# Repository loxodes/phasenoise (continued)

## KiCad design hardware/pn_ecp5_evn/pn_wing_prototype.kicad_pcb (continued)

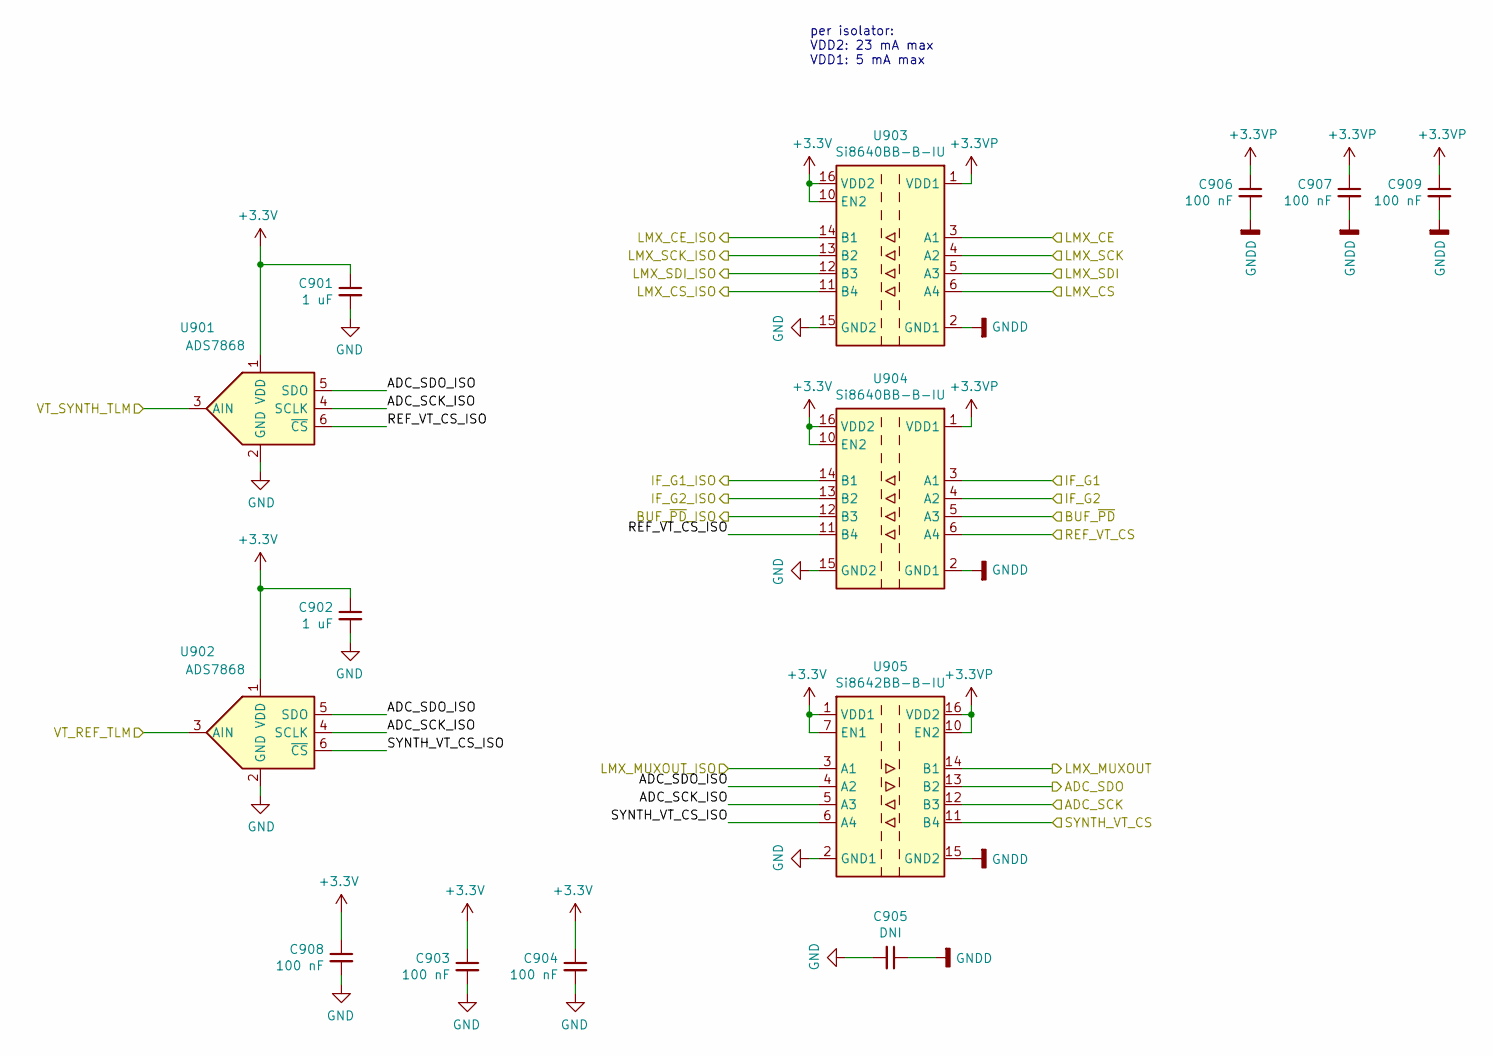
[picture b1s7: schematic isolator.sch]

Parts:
C901, C902: 1 uF; C_0402_1005Metric
C903, C904, C906, C907, C908, C909: 100 nF; C_0402_1005Metric
C905: DNI; C_0402_1005Metric
U901, U902: ADS7868; TSOT-23-6
U903, U904: Si8640BB-B-IU; QSOP-16_3.9x4.9mm_P0.635mm
U905: Si8642BB-B-IU; QSOP-16_3.9x4.9mm_P0.635mm

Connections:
+3.3VP: C906.1, C907.1, C909.1, U903.1 (VDD1), U904.1 (VDD1), U905.10 (EN2), U905.16 (VDD2); also elsewhere on the board
/BUF_~PD: U904.12 (B3); also elsewhere on the board
/IF_G1: U904.14 (B1); also elsewhere on the board
/IF_G2: U904.13 (B2); also elsewhere on the board
/LMX_CE: U903.14 (B1); also elsewhere on the board
/LMX_CSB: U903.11 (B4); also elsewhere on the board
/LMX_MUXout: U905.3 (A1); also elsewhere on the board
/LMX_SCK: U903.13 (B2); also elsewhere on the board
/LMX_SDI: U903.12 (B3); also elsewhere on the board
/VT_REF_TLM: U902.3 (AIN); also elsewhere on the board
/VT_SYNTH_TLM: U901.3 (AIN); also elsewhere on the board
/isolator/ADC_SCK: U905.12 (B3); also elsewhere on the board
/isolator/ADC_SCK_ISO: U901.4 (SCLK), U902.4 (SCLK), U905.5 (A3)
/isolator/ADC_SDO: U905.13 (B2); also elsewhere on the board
/isolator/ADC_SDO_ISO: U901.5 (SDO), U902.5 (SDO), U905.4 (A2)
/isolator/BUF_~PD: U904.5 (A3); also elsewhere on the board
/isolator/IF_G1: U904.3 (A1); also elsewhere on the board
/isolator/IF_G2: U904.4 (A2); also elsewhere on the board
/isolator/LMX_CE: U903.3 (A1); also elsewhere on the board
/isolator/LMX_CS: U903.6 (A4); also elsewhere on the board
/isolator/LMX_MUXOUT: U905.14 (B1); also elsewhere on the board
/isolator/LMX_SCK: U903.4 (A2); also elsewhere on the board
/isolator/LMX_SDI: U903.5 (A3); also elsewhere on the board
/isolator/REF_VT_CS: U904.6 (A4); also elsewhere on the board
/isolator/REF_VT_CS_ISO: U901.6 (~CS), U904.11 (B4)
/isolator/SYNTH_VT_CS: U905.11 (B4); also elsewhere on the board
/isolator/SYNTH_VT_CS_ISO: U902.6 (~CS), U905.6 (A4)
GND: C901.2, C902.2, C903.2, C904.2, C905.2, C908.2, U901.2 (GND), U902.2 (GND), U903.9 (GND2), U903.15 (GND2), U904.9 (GND2), U904.15 (GND2), U905.2 (GND1), U905.8 (GND1); also elsewhere on the board
GNDD: C905.1, C906.2, C907.2, C909.2, U903.2 (GND1), U903.8 (GND1), U904.2 (GND1), U904.8 (GND1), U905.9 (GND2), U905.15 (GND2); also elsewhere on the board

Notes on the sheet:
per isolator: VDD2: 23 mA max VDD1: 5 mA max

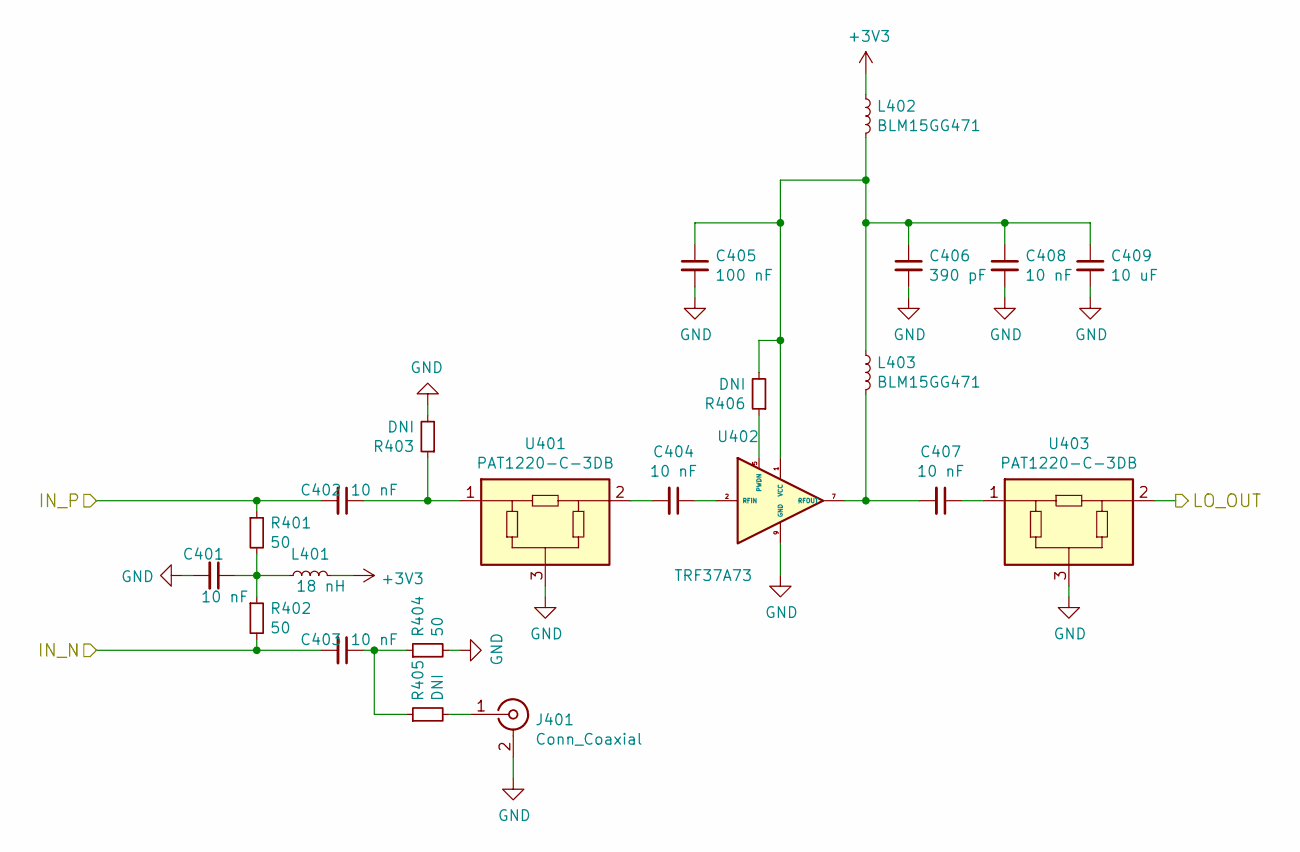
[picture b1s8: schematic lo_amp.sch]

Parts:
C301, C302, C303, C304, C307, C308: 10 nF; C_0402_1005Metric
C305: 100 nF; C_0402_1005Metric
C306: 390 pF; C_0603_1608Metric
C309: 10 uF; C_0603_1608Metric
J401: Conn_Coaxial; U.FL_Hirose_U.FL-R-SMT-1_Vertical
L301: 18 nH; L_0402_1005Metric
L302, L303: BLM15GG471; L_0402_1005Metric
R301, R302, R304: 50; R_0402_1005Metric
R303, R305, R306: DNI; R_0402_1005Metric
U301, U303: PAT1220-C-3DB; RF_Attenuator_Susumu_PAT1220
U302: TRF37A73; WSON-8-1EP_2x2mm_P0.5mm_EP0.9x1.6mm

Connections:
/rf_path/LO_IN: U303.2; also elsewhere on the board
/synth/lo_amp/IN_N: C303.2, R302.2; also elsewhere on the board
/synth/lo_amp/IN_P: C302.2, R301.1; also elsewhere on the board
GND: C301.2, C305.2, C306.2, C308.2, C309.2, J401.2 (Ext), R303.2, R304.2, U301.3, U302.9 (GND), U303.3; also elsewhere on the board
unnamed: C301.1, L301.1, R301.2, R302.1
unnamed: C302.1, R303.1, U301.1
unnamed: C303.1, R304.1, R305.1
unnamed: C304.1, U302.2 (RFIN)
unnamed: C304.2, U301.2
unnamed: C305.1, C306.1, C308.1, C309.1, L302.2, L303.1, R306.2, U302.1 (VCC)
unnamed: C307.1, U303.1
unnamed: C307.2, L303.2, U302.7 (RFOUT)
unnamed: R306.1, U302.5 (PWDN)

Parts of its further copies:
C401, C402, C403, C404, C407, C408: 10 nF; C_0402_1005Metric
C405: 100 nF; C_0402_1005Metric
C406: 390 pF; C_0603_1608Metric
C409: 10 uF; C_0603_1608Metric
J301: Conn_Coaxial; U.FL_Hirose_U.FL-R-SMT-1_Vertical
L401: 18 nH; L_0402_1005Metric
L402, L403: BLM15GG471; L_0402_1005Metric
R401, R402, R404: 50; R_0402_1005Metric
R403, R405, R406: DNI; R_0402_1005Metric
U401, U403: PAT1220-C-3DB; RF_Attenuator_Susumu_PAT1220
U402: TRF37A73; WSON-8-1EP_2x2mm_P0.5mm_EP0.9x1.6mm

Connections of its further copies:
/synth/aux_output/IN_N: C403.2, R402.2; also elsewhere on the board
/synth/aux_output/IN_P: C402.2, R401.1; also elsewhere on the board
/synth/aux_output/LO_OUT: U403.2; also elsewhere on the board
GND: C401.2, C405.2, C406.2, C408.2, C409.2, J301.2 (Ext), R403.2, R404.2, U401.3, U402.9 (GND), U403.3; also elsewhere on the board
unnamed: C401.1, L401.1, R401.2, R402.1
unnamed: C402.1, R403.1, U401.1
unnamed: C403.1, R404.1, R405.1
unnamed: C404.1, U402.2 (RFIN)
unnamed: C404.2, U401.2
unnamed: C405.1, C406.1, C408.1, C409.1, L402.2, L403.1, R406.2, U402.1 (VCC)
unnamed: C407.1, U403.1
unnamed: C407.2, L403.2, U402.7 (RFOUT)
unnamed: R406.1, U402.5 (PWDN)

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
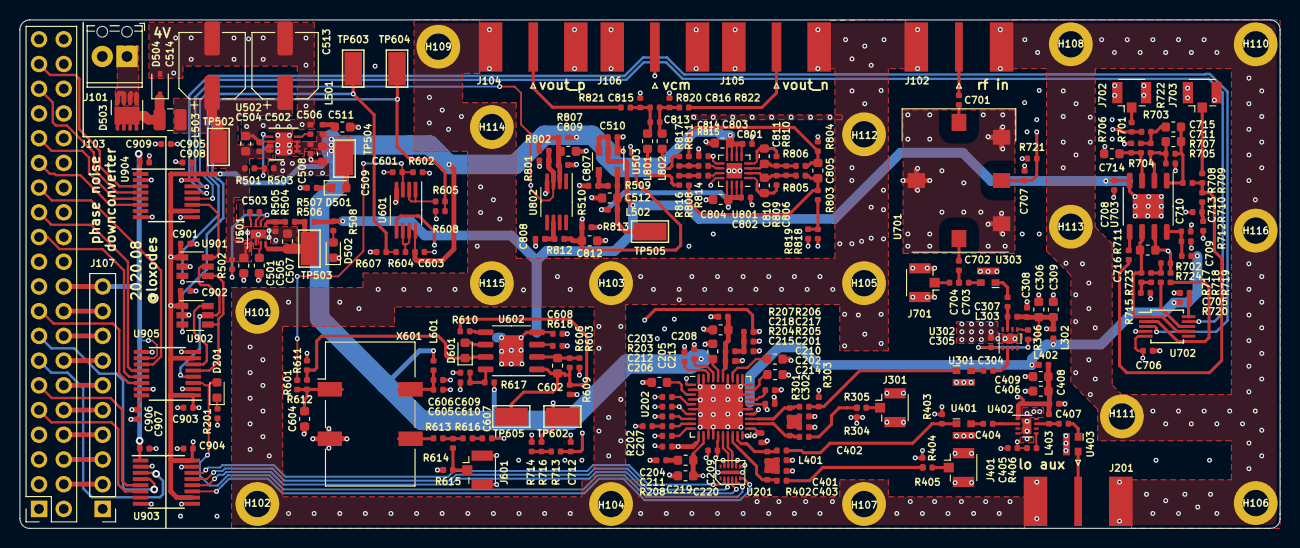
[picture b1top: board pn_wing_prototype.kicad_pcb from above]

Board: 4 copper layers, 129.5 x 52.2 mm, 277 parts (0 on the bottom side), 167 nets.

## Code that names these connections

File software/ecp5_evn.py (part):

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            ),

            ("pn_control", 0,
                Subsignal("if_g1",  Pins("A15")),
                Subsignal("if_g2",  Pins("H2")),
                Subsignal("buf_pd", Pins("J3")),
                Subsignal("synth_ce", Pins("N2")),
                IOStandard("LVCMOS33")
            ),
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        # Phase noise downconverter, control lines
        self.add_csr("pn_gpio")
        pn_control = platform.request("pn_control")
        self.submodules.pn_gpio = GPIOOut(Cat([pn_control.if_g1, pn_control.if_g2, pn_control.buf_pd, pn_control.synth_ce]))

        # ADC SPI bus ------------------------------------------------------------------------------
        # max SPI frequency is 20 MHz
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
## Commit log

2020-08-10 added initial schematic of phase noise analyzer - in progress
2020-08-10 first pass footprint assignment on pn r0
2020-08-17 started component placement on phase noise analyzer
2020-08-23 component placement on phase noise downconverter
2020-08-23 first pass component placement on phase noise downconverter
2020-08-24 work on routing phase noise downconverter
2020-08-25 layout of phase noise downconverter
2020-08-27 all nets connected in layout
2020-08-28 finished silkscreen cleanup, added via stitching
2020-08-28 added bottom layer ground plane, via cleanup
2020-08-28 drc and erc check, schematic cleanup
2020-08-29 checked stability of LO amplifier, started migen project, added more flexibility for active filtering on baseband path
2020-08-29 final layout cleanup, ordered phase noise downconverter boards
2020-08-30 added part numbers to schematic of phase noise downconverter, ordered
2020-09-05 added assembly drawing
2020-09-14 started writing ddc in migen
2020-09-15 start testing cic filter
2020-09-16 starting to hook together ddc, untested
2020-09-16 added schematic export, updated README, schematic cleanup
2020-09-16 Updated README to point to schematic
2020-09-17 corrected wiring on ddc..
2020-09-26 started on lmx2594 drivers
2020-09-27 commincation with on-board synth works, fixed spi and fpga pin mapping
2020-10-18 fixed rectifier circuit, inverted first lna to cancel out inverting integrator..
2020-10-25 fix integrator in reference pll..
2020-10-30 updated schematic export with pll fix
2020-11-28 fix ddc - use signed signals...
